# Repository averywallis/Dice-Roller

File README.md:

# Dice Roller
 KiCad files for a simple dice roller using LEDs and an Arduino

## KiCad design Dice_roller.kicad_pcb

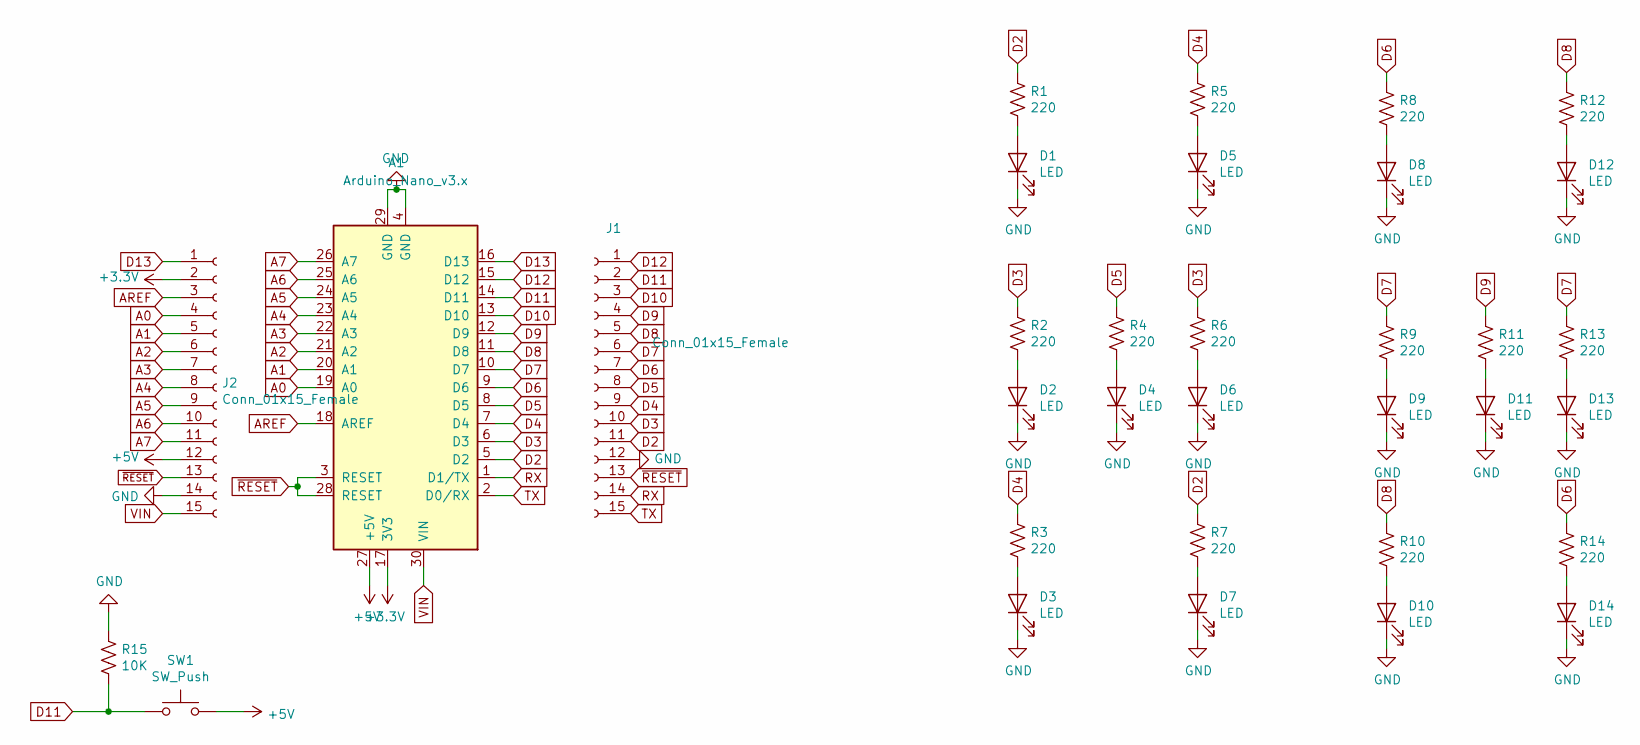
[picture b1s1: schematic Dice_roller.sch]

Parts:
A1: Arduino_Nano_v3.x
D1, D2, D3, D4, D5, D6, D7, D8, D9, D10, D11, D12, D13, D14: LED; LED_D3.0mm
J1, J2: Conn_01x15_Female; PinSocket_1x15_P2.54mm_Vertical
R1, R2, R3, R4, R5, R6, R7, R8, R9, R10, R11, R12, R13, R14: 220; R_0805_2012Metric_Pad1.15x1.40mm_HandSolder
R15: 10K; R_0805_2012Metric_Pad1.15x1.40mm_HandSolder
SW1: SW_Push; SW_PUSH_6mm

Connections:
+3V3: A1.17 (3V3), J2.2
+5V: A1.27 (+5V), J2.12, SW1.2
A0: A1.19 (A0), J2.4
A1: A1.20 (A1), J2.5
A2: A1.21 (A2), J2.6
A3: A1.22 (A3), J2.7
A4: A1.23 (A4), J2.8
A5: A1.24 (A5), J2.9
A6: A1.25 (A6), J2.10
A7: A1.26 (A7), J2.11
AREF: A1.18 (AREF), J2.3
D2: A1.5 (D2), J1.11, R1.1, R7.1
D3: A1.6 (D3), J1.10, R2.1, R6.1
D4: A1.7 (D4), J1.9, R3.1, R5.1
D5: A1.8 (D5), J1.8, R4.1
D6: A1.9 (D6), J1.7, R8.1, R14.1
D7: A1.10 (D7), J1.6, R9.1, R13.1
D8: A1.11 (D8), J1.5, R10.1, R12.1
D9: A1.12 (D9), J1.4, R11.1
D10: A1.13 (D10), J1.3
D11: A1.14 (D11), J1.2, R15.2, SW1.1
D12: A1.15 (D12), J1.1
D13: A1.16 (D13), J2.1
GND: A1.4 (GND), A1.29 (GND), D1.1 (K), D2.1 (K), D3.1 (K), D4.1 (K), D5.1 (K), D6.1 (K), D7.1 (K), D8.1 (K), D9.1 (K), D10.1 (K), D11.1 (K), D12.1 (K), D13.1 (K), D14.1 (K), J1.12, J2.14, R15.1
unnamed: D1.2 (A), R1.2
unnamed: D2.2 (A), R2.2
unnamed: D3.2 (A), R3.2
unnamed: D4.2 (A), R4.2
unnamed: D5.2 (A), R5.2
unnamed: D6.2 (A), R6.2
unnamed: D7.2 (A), R7.2
unnamed: D8.2 (A), R8.2
unnamed: D9.2 (A), R9.2
unnamed: D10.2 (A), R10.2
unnamed: D11.2 (A), R11.2
unnamed: D12.2 (A), R12.2
unnamed: D13.2 (A), R13.2
unnamed: D14.2 (A), R14.2
RX: A1.1 (D1/TX), J1.14
TX: A1.2 (D0/RX), J1.15
VIN: A1.30 (VIN), J2.15
~RESET: A1.3 (RESET), A1.28 (RESET), J1.13, J2.13

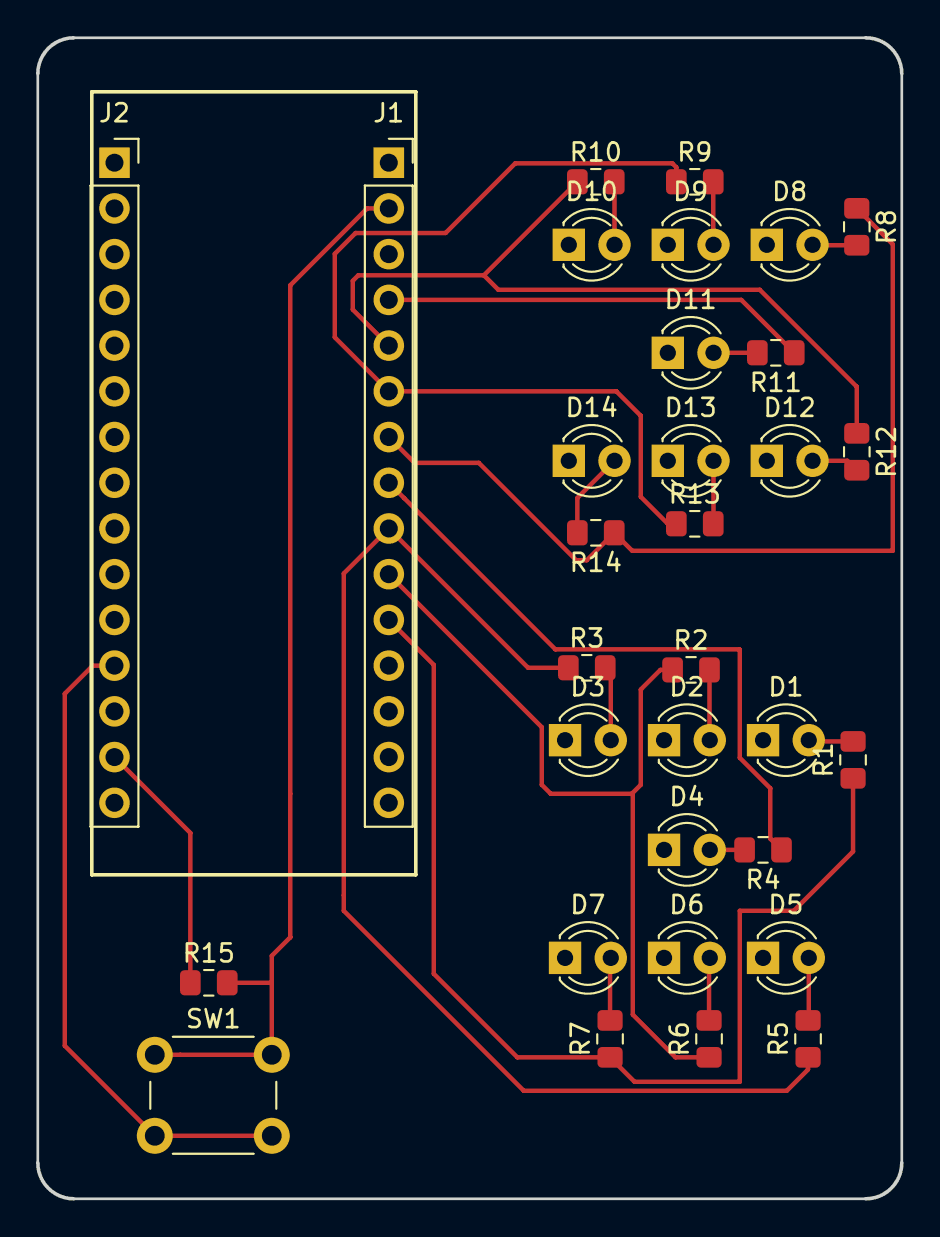
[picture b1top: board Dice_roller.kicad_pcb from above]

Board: 2 copper layers, 48.0 x 64.5 mm, 32 parts (0 on the bottom side), 26 nets.

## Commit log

2020-01-06 Reorganizing Github
2022-01-29 Create LICENSE
